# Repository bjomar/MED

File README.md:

# Motorcycle Accessory Distribution

This project is a KiCad PCB for switching and distributing a motorcycle's
12 V electrical supply to several accessory connections. Typical loads include
USB chargers, heated grips or seats, and auxiliary lighting.

## Features

- fused 12 V input using an automotive blade fuse
- accessory outputs switched by an automotive relay
- flyback diode protecting the control input from the relay coil
- shared ground distribution
- multiple screw-terminal and optional direct-solder outputs
- high-current layout using large copper zones
- enclosure models and production-ready Gerber files

## Connections

- **12V IN:** connect directly to the permanent battery-positive supply.
- **GND:** connect to battery negative or a suitable vehicle ground point.
- **CTRL 12V:** connect to a switched 12 V control signal, for example the
  ignition-switched accessory supply. This input energizes the relay coil; it
  does not carry the accessory load current.
- **PER1 to PER6:** switched accessory outputs. Observe the `+` and `-`
  markings printed next to each output.

Both positions of each two-pole input terminal are connected in parallel on
the PCB. They belong to the same electrical net and are not separate inputs.

Minimal connection diagram:

```text
Battery + (permanent) ---- 12V IN ---- Fuse ---- Relay ---- + PER1..PER6
Battery - / chassis ------ GND --------------------------- - PER1..PER6
Ignition-switched +12 V -- CTRL 12V ---- Relay coil
```

When `CTRL 12V` is active, the relay connects the fused permanent supply to
the positive peripheral outputs. Removing the control voltage switches all
outputs off.

## Current Rating and Fusing

The PCB is designed around a theoretical maximum total current of 30 A. This
rating is not verified for a PCB manufactured with 1 oz copper. For 1 oz
copper, a maximum fuse rating of **20 A is recommended**. A 30 A fuse should
only be considered with 2 oz copper and suitably rated wiring, connectors,
assembly, and thermal conditions.

Select the installed blade fuse to match the actual PCB copper weight and the
complete wiring harness. The fuse legend on the PCB allows the assembled
variant to be marked.

The copper paths, specified screw terminals, and optional solder-wire holes
are dimensioned so that each individual output can theoretically carry the
full board current. This permits high-current accessories such as heated grips
or a heated seat, provided the total load remains within the selected fuse and
board rating.

**There is only one overcurrent fuse on the PCB. The outputs are not fused
individually.** Each accessory branch must provide suitable overcurrent and
short-circuit protection for its own device and wiring. An internal fuse in an
accessory does not protect the cable between this board and that fuse; where
the branch cable cannot safely carry the main fuse current, install a separate
branch fuse close to the board.

## Enclosure

[`box.scad`](box.scad) is a minimal example enclosure rather than a finished
vehicle-qualified design. Its current geometry covers the three optional
direct-solder output connections, so those connections are inaccessible when
this example enclosure is used without modification. The three screw-terminal
outputs remain the intended accessible connections.

## Regulatory and Commercial Use

This is a privately developed, non-commercial open-source hardware project and
reference design. It has not undergone a conformity assessment, certification,
regulatory approval, automotive qualification, type approval, or independent
safety or EMC testing for any country or market. It carries no CE, UKCA, FCC,
UL, E-mark, or other regulatory approval, and no claim is made that the design
complies with the requirements of any particular jurisdiction or application.

The MIT License permits commercial use of the design files, but it does not
certify a resulting product or transfer responsibility for regulatory and
product compliance. Anyone who manufactures, modifies, integrates, imports,
distributes, sells, installs, or places a product based on this project on any
market is responsible for determining and fulfilling all requirements that
apply to their role, the finished product, its intended use, and every target
market. Depending on the jurisdiction, these may include testing, conformity
assessment, technical documentation, declarations, labeling and markings,
traceability, instructions, product safety, EMC, environmental requirements,
and vehicle or road-use approvals.

No certification or conformity mark may be inferred from the availability of
these design files. Any required mark or declaration must be issued by the
responsible economic operator only after the applicable procedure for the
finished product has been completed. This notice is not legal advice.

## License

This project is licensed under the [MIT License](LICENSE). Use, modification,
distribution, and commercial use are permitted under its terms. Manufacturer
datasheets in `datasheets/` remain the property of their respective rights
holders.

## Known Issue

**The `DZ85AB-5-PCB` relay socket footprint is incorrect.**

Do not manufacture the current PCB without verifying this footprint. Before a
new order, measure the actual relay socket pin and hole pattern or compare it
against a reliable manufacturer drawing, then correct the footprint.

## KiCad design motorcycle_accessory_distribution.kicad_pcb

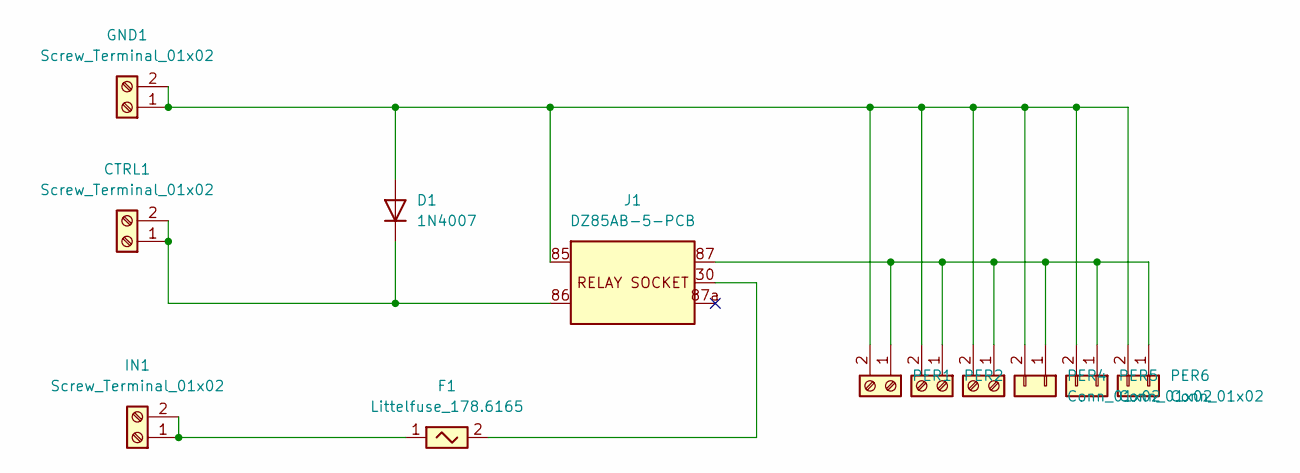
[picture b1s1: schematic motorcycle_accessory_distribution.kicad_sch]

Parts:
CTRL1: Screw_Terminal_01x02; PHOENIX_1868076
D1: 1N4007; D_DO-41_SOD81_P10.16mm_Horizontal
F1: Littelfuse_178.6165; Fuseholder_Littelfuse_178.6165
GND1: Screw_Terminal_01x02; PHOENIX_1868076
IN1: Screw_Terminal_01x02; PHOENIX_1868076
J1: DZ85AB-5-PCB
PER1, PER2, PER3: Screw_Terminal_01x02; PHOENIX_1868076
PER4, PER5, PER6: Conn_01x02; SolderWire-4sqmm_1x02_P12mm_D3mm_OD6mm

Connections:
unnamed: CTRL1.1, CTRL1.2, D1.1 (K), J1.86 (Coil)
unnamed: D1.2 (A), GND1.1, GND1.2, J1.85 (Coil), PER1.2, PER2.2, PER3.2, PER4.2, PER5.2, PER6.2
unnamed: F1.1, IN1.1, IN1.2
unnamed: F1.2, J1.30 (Common)
unnamed: J1.87 (Normally_open), PER1.1, PER2.1, PER3.1, PER4.1, PER5.1, PER6.1

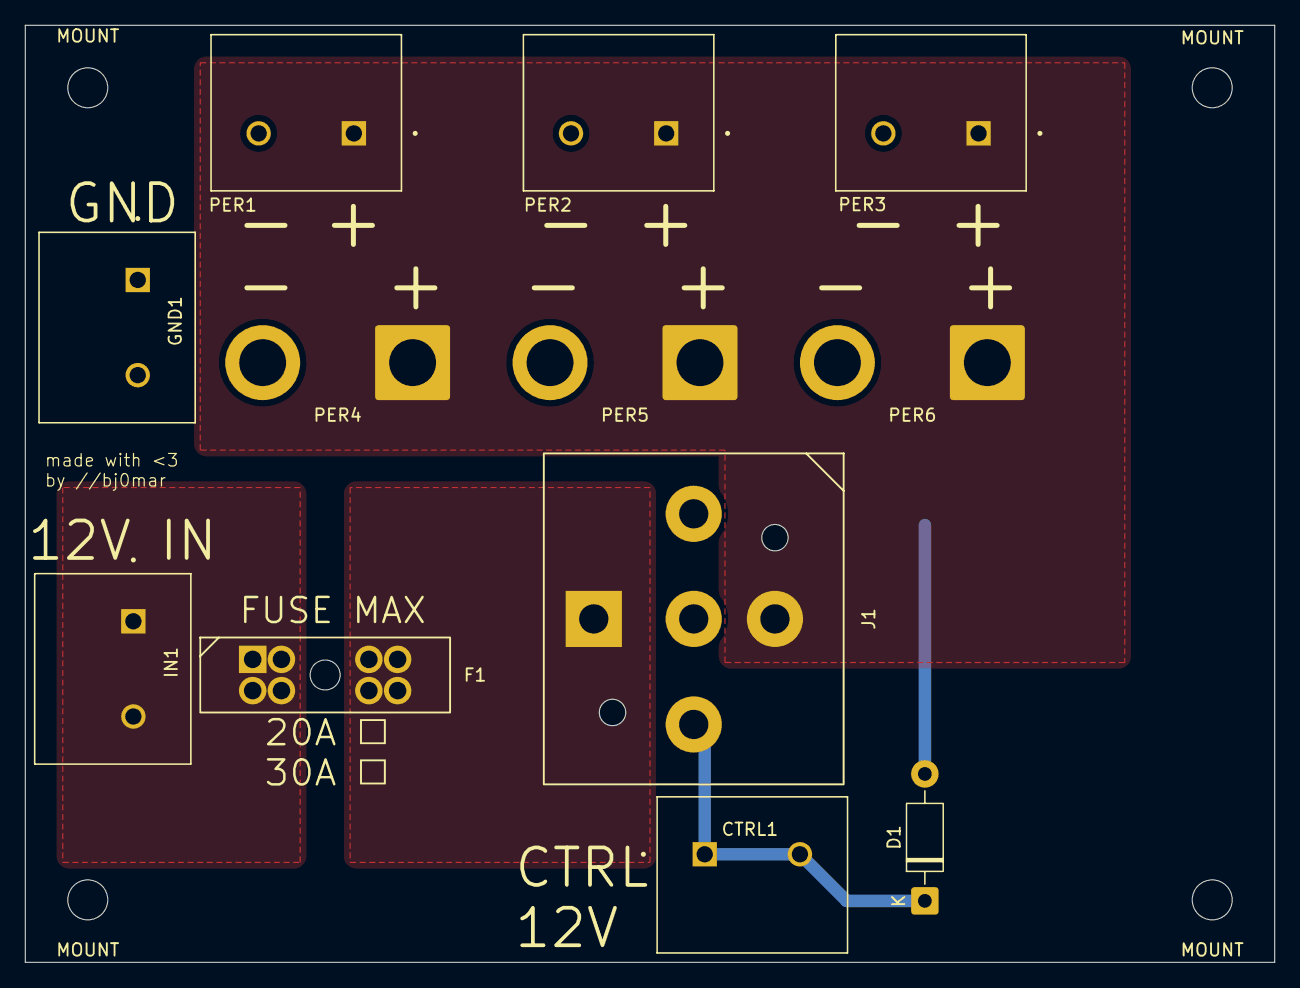
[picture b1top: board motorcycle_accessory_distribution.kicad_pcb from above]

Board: 2 copper layers, 100.0 x 75.0 mm, 16 parts (0 on the bottom side), 5 nets.

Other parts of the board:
MOUNT: MountingHole_3.2mm_M3
MOUNT#2, MOUNT#3, MOUNT#4: MountingHole_3.2mm_M3
